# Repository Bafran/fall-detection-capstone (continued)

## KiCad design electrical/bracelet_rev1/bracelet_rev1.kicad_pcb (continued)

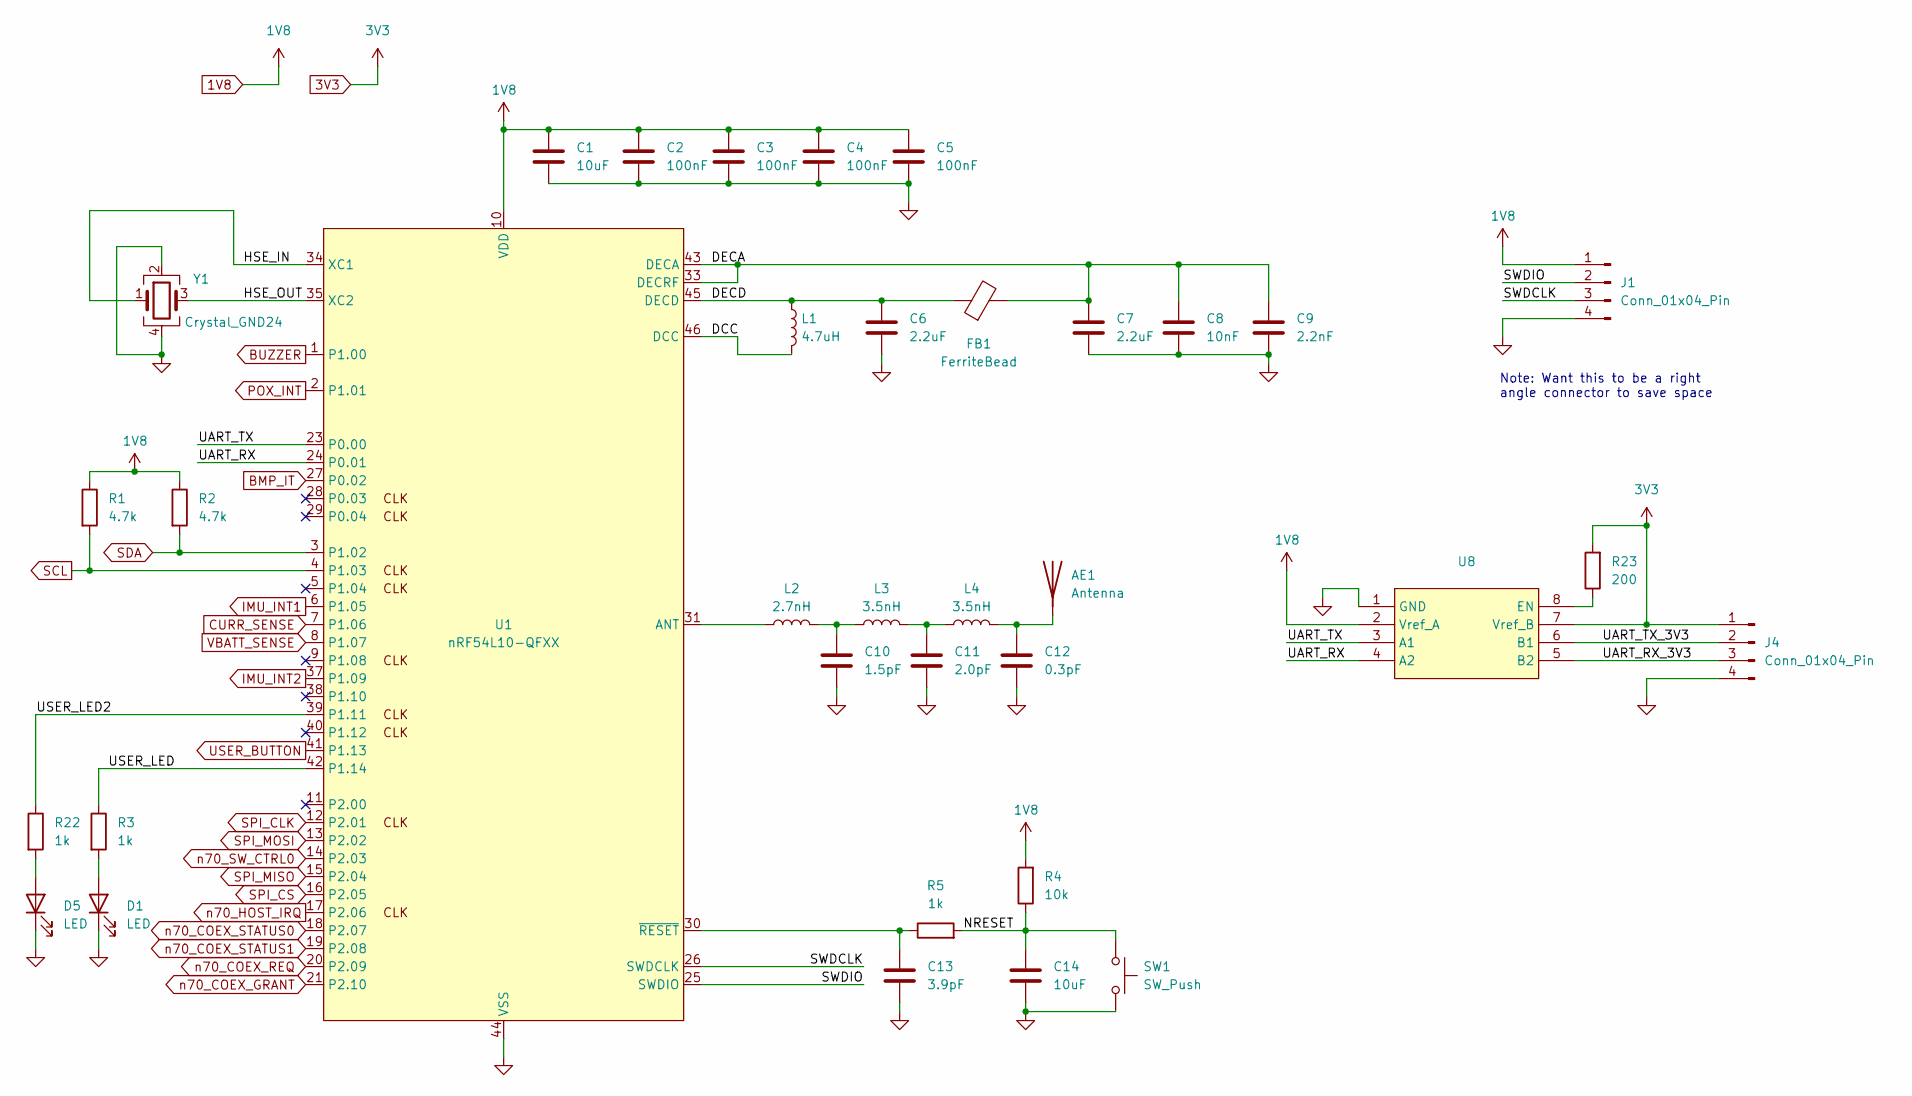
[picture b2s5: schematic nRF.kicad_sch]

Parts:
AE1: Antenna
C1, C14: 10uF; C_0603_1608Metric_Pad1.08x0.95mm_HandSolder
C2, C3, C4, C5: 100nF; C_0603_1608Metric_Pad1.08x0.95mm_HandSolder
C6, C7: 2.2uF; C_0603_1608Metric_Pad1.08x0.95mm_HandSolder
C8: 10nF; C_0603_1608Metric_Pad1.08x0.95mm_HandSolder
C9: 2.2nF; C_0603_1608Metric_Pad1.08x0.95mm_HandSolder
C10: 1.5pF; C_0603_1608Metric_Pad1.08x0.95mm_HandSolder
C11: 2.0pF; C_0603_1608Metric_Pad1.08x0.95mm_HandSolder
C12: 0.3pF; C_0603_1608Metric_Pad1.08x0.95mm_HandSolder
C13: 3.9pF; C_0603_1608Metric_Pad1.08x0.95mm_HandSolder
D1, D5: LED; LED_0603_1608Metric_Pad1.05x0.95mm_HandSolder
FB1: FerriteBead; L_0603_1608Metric_Pad1.05x0.95mm_HandSolder
J1, J4: Conn_01x04_Pin; PinHeader_1x04_P2.54mm_Vertical
L1: 4.7uH; L_0603_1608Metric_Pad1.05x0.95mm_HandSolder
L2: 2.7nH; L_0603_1608Metric_Pad1.05x0.95mm_HandSolder
L3, L4: 3.5nH; L_0603_1608Metric_Pad1.05x0.95mm_HandSolder
R1, R2: 4.7k; R_0603_1608Metric_Pad0.98x0.95mm_HandSolder
R3, R5: 1k; R_0603_1608Metric_Pad0.98x0.95mm_HandSolder
R4: 10k; R_0603_1608Metric_Pad0.98x0.95mm_HandSolder
R22: 1k; R_0201_0603Metric_Pad0.64x0.40mm_HandSolder
R23: 200; R_0201_0603Metric_Pad0.64x0.40mm_HandSolder
SW1: SW_Push
U1: nRF54L10-QFXX; QFN-48-1EP_6x6mm_P0.4mm_EP4.6x4.6mm
U8: (no value)
Y1: Crystal_GND24; Crystal_SMD_3225-4Pin_3.2x2.5mm_HandSoldering

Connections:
3V3: J4.1, R23.2, U8.7 (Vref_B); also elsewhere on the board
/nRF/DCC: L1.2, U1.46 (DCC)
/nRF/DECA: C7.1, C8.1, C9.1, FB1.2, U1.33 (DECRF), U1.43 (DECA)
/nRF/DECD: C6.1, FB1.1, L1.1, U1.45 (DECD)
/nRF/HSE_IN: U1.34 (XC1), Y1.1
/nRF/HSE_OUT: U1.35 (XC2), Y1.3
/nRF/NRESET: C14.1, R4.1, R5.2, SW1.1
/nRF/SWDCLK: J1.3, U1.26 (SWDCLK)
/nRF/SWDIO: J1.2, U1.25 (SWDIO)
/nRF/UART_RX: U1.24 (P0.01), U8.4 (A2)
/nRF/UART_RX_3V3: J4.3, U8.5 (B2)
/nRF/UART_TX: U1.23 (P0.00), U8.3 (A1)
/nRF/UART_TX_3V3: J4.2, U8.6 (B1)
/nRF/USER_LED: R3.1, U1.42 (P1.14)
/nRF/USER_LED2: R22.1, U1.39 (P1.11)
BMP_IT: U1.27 (P0.02)
BUZZER: U1.1 (P1.00)
CURR_SENSE: U1.7 (P1.06); also elsewhere on the board
GND: C1.2, C2.2, C3.2, C4.2, C5.2, C6.2, C7.2, C8.2, C9.2, C10.2, C11.2, C12.2, C13.2, C14.2, D1.1 (K), D5.1 (K), J1.4, J4.4, SW1.2, U1.32 (VSS_PA), U1.44 (VSS), U1.49 (VSS), U8.1 (GND), Y1.2, Y1.4; also elsewhere on the board
IMU_INT1: U1.6 (P1.05); also elsewhere on the board
IMU_INT2: U1.37 (P1.09); also elsewhere on the board
unnamed: AE1.1, C12.1, L4.2
unnamed: C10.1, L2.2, L3.1
unnamed: C11.1, L3.2, L4.1
unnamed: D1.2 (A), R3.2
unnamed: D5.2 (A), R22.2
unnamed: L2.1, U1.31 (ANT)
unnamed: C13.1, R5.1, U1.30 (~RESET)
unnamed: R23.1, U8.8 (EN)
POX_INT: U1.2 (P1.01); also elsewhere on the board
SCL: R1.2, U1.4 (P1.03); also elsewhere on the board
SDA: R2.2, U1.3 (P1.02); also elsewhere on the board
SPI_CLK: U1.12 (P2.01); also elsewhere on the board
SPI_CS: U1.16 (P2.05); also elsewhere on the board
SPI_MISO: U1.15 (P2.04); also elsewhere on the board
SPI_MOSI: U1.13 (P2.02); also elsewhere on the board
USER_BUTTON: U1.41 (P1.13); also elsewhere on the board
VBATT_SENSE: U1.8 (P1.07); also elsewhere on the board
n70_COEX_GRANT: U1.21 (P2.10); also elsewhere on the board
n70_COEX_REQ: U1.20 (P2.09); also elsewhere on the board
n70_COEX_STATUS0: U1.18 (P2.07); also elsewhere on the board
n70_COEX_STATUS1: U1.19 (P2.08); also elsewhere on the board
n70_HOST_IRQ: U1.17 (P2.06); also elsewhere on the board
n70_SW_CTRL0: U1.14 (P2.03); also elsewhere on the board

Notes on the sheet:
Note: Want this to be a right angle connector to save space

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
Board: 2 copper layers, 101 parts (0 on the bottom side), 66 nets, no tracks yet.

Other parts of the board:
D4#2: WS2812B; LED_WS2812B_PLCC4_5.0x5.0mm_P3.2mm

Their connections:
3V3: D4#2.1 (VDD); also elsewhere on the board
GND: D4#2.3 (VSS); also elsewhere on the board

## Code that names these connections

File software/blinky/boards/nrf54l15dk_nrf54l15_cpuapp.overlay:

/delete-node/ &button3;
/delete-node/ &button2;
/delete-node/ &button1;
/delete-node/ &led3;
/delete-node/ &led2;
/delete-node/ &led1;

/ {
		aliases {
			/delete-property/ led1;
			/delete-property/ led2;
			/delete-property/ led3;
			/delete-property/ button1;
			/delete-property/ button2;
			/delete-property/ button3;
		/delete-property/ sw1;
		/delete-property/ sw2;
		/delete-property/ sw3;
		/delete-property/ pwm-led0;
		};

	leds {
		led1 {
			label = "led1";
			gpios = <&gpio1 11 0>;
		};
	};
};

&pwm_led1 {
	/delete-property/ pwms;
};
/delete-node/ &{/pin-controller/pwm20_default/group1/};

&clock {
	status = "okay";
};

&i2c30 {
	max3010x@57 {
		compatible = "maxim,max30101";
		reg = <0x57>;
	};

	status = "okay";
	pinctrl-0 = <&i2c30_default>;
	pinctrl-1 = <&i2c30_sleep>;
	pinctrl-names = "default", "sleep";
};

&pinctrl {
	i2c30_default: i2c30_default {
		group1 {
			psels = <NRF_PSEL(TWIM_SDA, 1, 2)>, <NRF_PSEL(TWIM_SCL, 1, 3)>;
		};
	};

	i2c30_sleep: i2c30_sleep {
		group1 {
			psels = <NRF_PSEL(TWIM_SDA, 1, 2)>;
		};
	};

	pwm21_default: pwm21_default {
		group1 {
			psels = <NRF_PSEL(PWM_OUT0, 1, 0)>;
		};
	};

	pwm21_sleep: pwm21_sleep {
		group1 {
			psels = <NRF_PSEL(PWM_OUT0, 1, 0)>;
		};
	};
};

&uart20 {
	status = "disabled";
};

&pwm20 {
	status = "okay";
};

&led0 {
	gpios = <&gpio1 14 0>;
};

/ {
	zephyr,user {
		max3010x_irq-gpios = <&gpio1 1 0>;
		lsm6ds3_irq1-gpios = <&gpio1 5 0>;
		lsm6ds3_irq2-gpios = <&gpio1 9 0>;
		current_sense_adc-gpios = <&gpio1 6 0>;
		vbatt_sense_adc-gpios = <&gpio1 7 0>;
		n70_host_irq-gpios = <&gpio2 6 0>;
		n70_coex_status0-gpios = <&gpio2 7 0>;
		n70_coex_status1-gpios = <&gpio2 8 0>;
		n70_coex_req-gpios = <&gpio2 9 0>;
		n70_coex_grant-gpios = <&gpio2 10 0>;
		n70_sw_ctrl0-gpios = <&gpio2 3 0>;
		bmp_irq-gpios = <&gpio0 2 0>;
	};
};

&pwm20_default {
	group1 {
		psels = <NRF_PSEL(PWM_OUT0, 1, 8)>;
	};
};

&pwm21 {
	status = "okay";
	pinctrl-0 = <&pwm21_default>;
	pinctrl-1 = <&pwm21_sleep>;
	pinctrl-names = "default", "sleep";
};

&spi00 {
	status = "okay";
};

&mx25r64 {
	status = "disabled";
};
/delete-node/ &{/pwmleds/};

&uart00 {
	status = "disabled";
};

&uart21 {
	status = "disabled";
};

&uart22 {
	status = "disabled";
};

&uart30 {
	status = "okay";
};

&uart30_default {
	group1 {
		psels = <NRF_PSEL(UART_TX, 0, 0)>;
	};

	group2 {
		psels = <NRF_PSEL(UART_RX, 0, 1)>;
	};
};

&uart30_sleep {
	group1 {
		psels = <NRF_PSEL(UART_TX, 0, 0)>, <NRF_PSEL(UART_RX, 0, 1)>;
	};
};

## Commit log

2025-11-15 KiCAD MCU initial commit
2025-11-15 Empty ESP32 file
2025-11-15 Copy Adafruit example code for IMU
2025-11-18 Changed IMU test code
2025-11-18 Add IMU to schematic
2025-11-19 Added power. It is a mess
2025-11-20 Organize schematic a bit
2025-11-22 Many schematic updates
2025-11-23 Mostly finihsed hopefully but still needs clean up anyway
2025-12-03 May updates
2025-12-03 Redo component numbers
2025-12-19 Updated Wi-Fi IC
2025-12-19 Setting up nRF54 pinout
2025-12-20 Updated more things
2025-12-20 Attempting to remove submodule
2025-12-20 Push blinky
2025-12-21 More schematic stuff
2025-12-22 ESP32 Sensor Module Schematic
2025-12-23 Layout attempt
2025-12-23 Layout attempt two. Routing started
2025-12-23 Routing mostly done i think
2025-12-26 Responding to comments
2025-12-26 Revised USB layout and ground pour on bottom layer
2025-12-26 Trace is no longer broken
2026-01-17 Pushing unsaved changes
2026-01-27 Updated IMU test code
2026-01-28 UDP receiver set up
2026-02-01 moved imu_test into sketch folder
2026-02-01 deleting old imu_test out of sketch folder
2026-02-01 esp-now connection between boards
2026-02-01 v_batt_sense and curr_sense
2026-02-01 Fixed sense code
2026-02-17 wirst ino added
2026-02-17 chest ino added
2026-03-05 UI Initial Commit
2026-03-05 added git ignore
2026-03-06 front end changes
2026-03-06 connect to front end
2026-03-10 Manual Fall Trigger Added to Chest sketch
2026-03-10 Added Battery Sensing and UDP receiver to web server
2026-03-10 Backend Server linked to Frontend
2026-03-10 Cancellation Button
2026-03-12 Added Blinky to chest and wrist code
2026-03-12 syntax
2026-03-12 fixed blinky
